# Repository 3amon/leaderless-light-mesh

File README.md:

# Leaderless light mesh

Firmware, tools, tests and hardware for small wearable LED rings that keep a
shared clock with no leader. Each ring is an nRF52840 running Zephyr and
OpenThread. Rings gossip their clocks to whoever is in radio range, agree on
who is standing together, and render the same animation on every member of
that group, pixel for pixel, with no ring in charge and nothing streamed.

People walk around. Groups split, merge and lose members all the time, so the
design treats every one of those as a non-event: there is no time master to
elect, lose or fail over.

The chart is a simulation, not a measurement: six nodes, each running the
firmware's own `clock_estimator.c`, in two groups that start 0.8 s apart and
come into range at t = 0. Data and the command that produced it are in
[`docs/data/`](docs/data/). The measured numbers are below.

## What is in here

- **A leaderless clock** in the style of GTSP (Sommer and Wattenhofer, 2009):
  every node keeps `global = h * local + theta`, pulls `theta` (phase) and `h`
  (rate) toward a trust-weighted median of its neighbours, and regresses rate
  on the neighbours' raw, never-adjusted clocks. Design in
  [`TIME-SYNC.md`](TIME-SYNC.md); wire format and policy in
  [`docs/firmware-architecture.md`](docs/firmware-architecture.md).
- **Group formation** from one-hop radio contact, with hysteresis, reciprocal
  topology and a timing gate, so "lit as a group" implies "visibly in sync".
- **Signed over-the-air updates** through MCUboot with automatic rollback, a
  transactional deployer, and a boot-recovery ladder that gets a hung node
  back to a USB drive without a button.
- **A carrier PCB** (KiCad) and **printed enclosures** (FreeCAD).
- **Fleet tools** that run on a Raspberry Pi border router.
- **Host tests and simulators** that compile the same C files the firmware
  ships.

## What was demonstrated, with numbers

Each number names the file that supports it. "Development repository" means
the private repository this was exported from; its history and its real
device inventory are not included here.

| | Number | Source |
|---|---|---|
| Sync measured optically, two rings | 301 paired LED flashes over five minutes at 30 fps: **3.59 ms** median offset, 3.11 ms MAD, -0.93 ms/min drift. A later run: 304 pairs, 4.42 ms, 3.35 ms MAD, +0.65 ms/min | `docs/development-plan.md`, "Execution log — 2026-07-21", Phase 6 |
| Same two rings before the sync engine existed | 47.8 ms apart (arbitrary phase) | `TIME-SYNC.md`, "Baseline measurement" |
| Recovery from a forced clock scramble, on camera | back in step 9.9 s after the scramble, 150 flash pairs | `evidence/hardware/2026-07-20/sync-tests/20260718-044700-scramble/result.json` |
| Fleet | 39 rings inventoried when the fleet was deployed (41 by the last commit); 24 is the designed cap for one group | development repository inventory (a 6-row sample is in `config/rings.json`); cap in `docs/firmware-architecture.md` |
| Largest group qualified on hardware | six rings re-forming one scene after a rollout; one deliberately scrambled ring was demoted in 24 s and readmitted 16 s after the abuse stopped | `docs/sync-cohesion-investigation.md`, "Live fleet qualification" |
| Largest group in simulation | 24 nodes cold-starting together converge in 29-36 s | `docs/gap-hunt-2026-08.md`, section 3 |
| Releases | 41 tagged releases, v0.1.16 to v0.1.93, over 268 commits from 2026-07-17 | development repository; process in `docs/releases.md` |
| Reproducible builds | two pristine builds byte-identical except the RSA-PSS signature salt | `docs/releases.md` |
| Fleet image size | 288,304 of 372,736 bytes flash (77.35%) at v0.1.16; the release gate is 92% | `docs/releases.md`, `scripts/check_firmware_size.py` |
| Reboot soak | 124 reboot trials archived, 121 passed, including 50/50 and 43/43 runs | `evidence/hardware/SUMMARY.md` |
| Forced rollback | final run 5/5: an image that refuses to confirm is reverted by MCUboot, in 119.86-120.63 s. Two earlier harness runs failed on their first trial and are kept | `evidence/hardware/SUMMARY.md`, `docs/development-plan.md` Phase 1 |
| USB/UF2 recovery | 36/36 trials | `evidence/hardware/SUMMARY.md` |
| OTA transactions | 28 per-device results archived: 12 `success`, 10 `already_current`, 5 `upload_failed` (uploads cut on purpose; none armed), 1 `rollback` (an image on an isolated partition that must not confirm) | `evidence/hardware/SUMMARY.md` |
| Recovery ladder | a deliberately hanging image presented itself as a USB drive 51 s after reset; the board was healthy 5.7 s after the file copy | `docs/boot-recovery-ladder.md` |
| Host tests | 212 Python tests; they build and run 22 C suites (131 test functions) against the firmware sources | `tests/`, run below |
| Simulators | 9 measurement harnesses (7 protocol, 2 rendering) plus the merge trace | `tests/c/campaign/`, `tests/c/bench/`, `tests/c/merge_trace.c` |

The archived evidence covers 2026-07-18 to 2026-07-20 and two rings. Later
results in the table are from the written record; their raw files stayed on
the gateway.

## What went wrong

- **A release was withdrawn.** v0.1.82 passed review and host tests, then
  wedged every board into its watchdog seconds after joining a live mesh: a
  struct had grown past the 4 KB main stack. v0.1.83 fixed it. The only
  "healthy" bench run of v0.1.82 had been on a quieted mesh that never
  exercised the path. `docs/gap-hunt-2026-08.md`, 2026-08-17 addendum.
- **The Rev A board has a pin-count error.** The module has 13 pins per side;
  the carrier was laid out for 12. Seated the obvious way it shorts RAW to
  ground. The battery connector is also routed to the wrong rail and must not
  be used. `docs/hardware-rev-a-errata.md`.
- **The "white flash" was a brownout.** A scene that lit every LED at once
  drew about six times the idle load for 370 ms, sagged the rail and turned
  the ring white. It looked like a colour bug and was invisible in any
  pixel-level simulation. The fix is a per-frame power budget found on the
  hardware (45 per LED); the first value tried (90) never engaged.
  `firmware/thread-ring/src/led_budget.h`, `tests/c/led_budget_test.c`.
- **A weighted mean let one liar capture the clock.** In simulation a crowd
  converged onto a node broadcasting a constant 10 s lie. The estimator now
  uses a weighted median, a snap quorum and minority-outlier rejection.
  `docs/sync-cohesion-investigation.md`.
- **A median tie-break ratcheted the fleet's rate trim** about +300 ppm per
  minute while phase stayed locked, so nothing looked wrong. Found in
  telemetry on seven live rings, reproduced in the simulator, fixed in
  v0.1.76 and kept as a regression test. Same document.
- **Still open.** An intermittent watchdog reset during the MCUboot image
  swap (`reset=00000012`) was never fixed; the node rolls back safely but the
  update does not land (`docs/onboarding-blank-boards.md`, "Failure
  signatures"). The battery-park branch of the recovery ladder was never
  qualified on hardware. Battery voltage cannot be read on Rev A.

## Limits of the evidence

- The camera measurement is of **two** rings on a bench. Larger groups were
  checked through firmware telemetry and by eye, not optically.
- Everything about 24-node behaviour is simulated.
- The simulators model the radio as per-link loss and jitter. They do not
  model 802.15.4 contention or body shadowing.
- The measurement harnesses in `tests/c/campaign/` assert nothing, and the
  engine has changed since `docs/gap-hunt-2026-08.md` was written, so their
  output today does not reproduce every figure in that report.
- The firmware in this export was **not built** as part of preparing it: the
  Thread credentials were replaced with placeholders, and a log string and a
  few comments were reworded. The host tests were run (below).

## Build, run, test

Host tests need Python 3.12 or newer and a C compiler (`cc`). No hardware, no
network.

```sh
uv run --no-project python -m unittest discover -s tests
```

212 tests; a few seconds. The simulators that print measurements:

```sh
SRC=firmware/thread-ring/src
cc -std=c11 -O2 -I$SRC -Itests/c -Itests/c/campaign \
   $SRC/group_engine.c $SRC/group_policy.c $SRC/social_scene.c \
   $SRC/peer_slot_policy.c $SRC/sync_schedule.c $SRC/clock_estimator.c \
   tests/c/campaign/integrated.c -lm -o /tmp/integrated && /tmp/integrated

cc -std=c11 -O2 -I$SRC -Itests/c $SRC/clock_estimator.c \
   tests/c/merge_trace.c -lm -o /tmp/merge_trace && /tmp/merge_trace | head
```

See `tests/c/campaign/README.md` and `tests/c/bench/README.md` for the rest.

Firmware needs Zephyr SDK 0.17.0 and the pinned workspace
(`west.yml`, `config/toolchain.lock.json`, `docs/releases.md`):

```sh
ZEPHYR_WORKSPACE=/path/to/zephyr-ws scripts/bootstrap_workspace.sh
scripts/build_firmware.sh debug
MCUBOOT_SIGNING_KEY=/secure/key.pem scripts/build_firmware.sh fleet
scripts/local_ci.sh        # the whole gate, including the native_sim test
```

Target board: a SuperMini nRF52840 (nice!nano-compatible) with the Adafruit
UF2 bootloader, Zephyr board `promicro_nrf52840/nrf52840/uf2`. Zephyr,
MCUboot, OpenThread and the UF2 bootloader are not vendored; `west` fetches
the first three.

### Network credentials

`firmware/thread-ring/prj.conf` carries **placeholder** Thread credentials:
the well-known example network key, PAN ID 0xABCD and Zephyr's default
extended PAN ID. A ring built with them will only join a network that uses
the same public values, which you should not run.

To use your own, change `CONFIG_OPENTHREAD_NETWORKKEY`, `CONFIG_OPENTHREAD_PANID`
and `CONFIG_OPENTHREAD_XPANID` (and the channel and name if you like) to match
your border router's active dataset. Keep the real values out of version
control: either edit `prj.conf` locally, or put the three lines in a private
Kconfig fragment and add it to the `EXTRA_CONF_FILE` list in
`scripts/build_firmware.sh`. The network key is the trust boundary between
rings, so treat it like a password.

### Other things you supply

- `config/rings.json` is a six-row sample with invented serial numbers and
  addresses. The fleet tools resolve every target through this file; replace
  it with your own devices.
- `config/release-signers.example` shows the allowed-signers format for
  release attestation. Copy it to `config/release-signers` with your own key.
- Firmware and release signing keys, and the per-device control keys, are
  never in the repository. `docs/security.md` describes where they live.
- The fleet tools expect a small dashboard service on the gateway
  (`http://localhost:8080`) for name lookup and heartbeat history. It belongs
  to a separate project and is not included; most tools also accept an IPv6
  address directly.

## Layout

| Path | Contents |
|---|---|
| `TIME-SYNC.md` | Protocol design notes |
| `docs/` | Architecture, release process, security model, errata, investigations. Index in `docs/README.md` |
| `firmware/thread-ring/` | The ring firmware (about 11,500 lines of C). Policy modules are pure C with no Zephyr dependencies |
| `firmware/ring-test/`, `firmware/settings-medic/` | Bring-up image and a settings-partition recovery image |
| `tests/` | Python tests; `tests/c/` C suites and simulators; `tests/zephyr/` native_sim boot/OTA test |
| `pi-tools/` | Fleet tools for the gateway: transactional deploy, control client, HIL harnesses, camera timing |
| `scripts/` | Build, release, signing, CI, workspace checks, USB helpers |
| `config/` | Sample inventory, HIL job definitions, toolchain lock |
| `patches/` | Tracked patches to MCUboot and Zephyr |
| `deploy/systemd/` | Sandboxed units for the HIL runner |
| `hardware/` | KiCad project, gerbers, BOM/CPL, renders |
| `enclosure/` | Printed enclosures and diffuser caps |
| `evidence/` | Archived hardware test results and a summary table |

## Not included, and why

- Git history and release binaries: the export is a snapshot of `main`.
- The real device inventory, control keys, signing keys and Thread
  credentials.
- Kernel logs and raw captures from the gateway (host output).
- Session handoff notes and one-off rollout scripts from the development
  repository.
- The gateway's operating-system setup and dashboard, which belong to a
  separate project.
- The two browser simulations the design was first worked out in.

## Licence

Code, tests, tools and documentation: MIT, see [`LICENSE`](LICENSE).
Hardware and enclosure design files: CC BY 4.0, see
[`LICENSE-hardware.md`](LICENSE-hardware.md). `patches/` modify Apache-2.0
projects and stay under that licence.

Copyright 2026 Eamon White <white.eamon@gmail.com>

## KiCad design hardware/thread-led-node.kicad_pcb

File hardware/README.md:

# Carrier PCB (Rev A)

KiCad 10 project for an 80 x 46 mm, 2-layer carrier that takes a SuperMini
nRF52840 module (a nice!nano-style "Pro Micro nRF52840" clone) and drives an
external WS2812B ring or strip. Design files are CC BY 4.0
(`../LICENSE-hardware.md`).

> **Rev A has two known errors. Read `../docs/hardware-rev-a-errata.md` before
> building one.**
>
> 1. The module has 13 positions per side (separate B-/B+ pins at the USB
>    end); the carrier was laid out with 12-position sockets. Seat the module
>    with B-/B+ hanging outside the sockets. Seating them in the sockets shifts
>    every pin by one and shorts RAW to ground.
> 2. J2+ is routed to RAW rather than the module's B+ charger terminal. Do not
>    connect a rechargeable battery to J2. USB and current-limited bench power
>    are verified; battery operation is not safe on Rev A.
>
> The silkscreen pin labels also print partly off the board edge.

## Files

| Path | Contents |
|---|---|
| `thread-led-node.kicad_sch`, `.kicad_pcb`, `.kicad_pro` | Schematic, board, project |
| `gerbers/` | Gerbers and Excellon drill files as sent to the fab |
| `assembly/` | BOM and placement (CPL) files for JLCPCB assembly |
| `fab_export.py` | Regenerates the fab package; computes placement centroids from pad bounding boxes and applies per-footprint rotation offsets (why: see `../docs/kicad-notes.md`) |
| `models/supermini_nrf52840.wrl` | Generated box-model stand-in for the module, used for the 3D render |
| `renders/` | 3D render, top view (PNG and SVG) |
| `thread-led-node.kicad_pcb.drc.json` | KiCad DRC report: 0 errors, 5 warnings (silkscreen), 0 unconnected |

`fab_export.py` needs KiCad's `pcbnew` Python module and `kicad-cli`. Footprints
and 3D models come from the stock KiCad libraries, which are not redistributed
here.

## Power path

- RAW -> F1 (1.1 A polyfuse) -> Q1 (AO3401A high-side switch, driven by Q2
  2N7002 with a 100 k pull-up, off at boot) -> J1 (JST-XH) to the LEDs.
- U2 (SN74LV1T34) level-shifts LED data and is powered from the fused,
  unswitched rail.
- Firmware must drive `EN_LED` (P0.17) high before the LED rail is live, wait
  for it to settle, and send black before turning it off.

## Pin map (SuperMini / nice!nano numbering)

| Signal | Pin | Board net |
|---|---|---|
| LED data out | P0.06 (J3-1) | LED_DATA_MCU -> U2 -> 330 ohm -> J1-2 |
| LED power enable | P0.17 (J3-5) | EN_LED (high = strip on) |
| USER button | P0.20 (J3-6) | BTN (to GND, internal pull-up) |
| Battery sense | P0.31 / AIN7 (J4-5) | VBAT_DIV. Measured floating on the tested modules: see the errata |

## Layout notes

- Sockets are placed so the module's USB-C face sits flush with the top board
  edge, for an enclosure wall.
- Copper pours on both layers are windowed out under the module's chip
  antenna.
- TP1 = VLED, TP2 = DIN, TP3 = GND. D3 lights when the LED rail is switched on.
- 4 x M2.5 mounting holes on a 68 x 34 mm pattern.

## BOM

| Ref | Part | LCSC |
|---|---|---|
| U2 | SN74LV1T34DBVR, SOT-23-5 | C100024 |
| Q1 | AO3401A P-FET, SOT-23 | C15127 |
| Q2 | 2N7002, SOT-23 | C8545 |
| F1 | 1206L110THYR polyfuse 1.1 A | C126818 |
| J1 | JST B3B-XH-A 3-pin | C144394 |
| J2 | JST-PH 2-pin | C126363 |
| J3, J4 | 1x12 2.54 mm female header | C7509522 |
| C1 | 100 nF 0603 | C14663 |
| C2 | 470 uF 16 V radial | C105296 |
| R1 | 330 ohm 0603 | C23138 |
| R2, R3 | 1 M 0603 | C22935 |
| R4 | 100 k 0603 | C25803 |
| R5 | 1 k 0603 | C21190 |
| D3 | red LED 0603 | C2286 |
| SW1 | 6x6 mm THT tactile | C42416242 |

Recorded cost for five assembled boards: PCB $2 + assembly $28.52, before
shipping (`../docs/kicad-notes.md`).

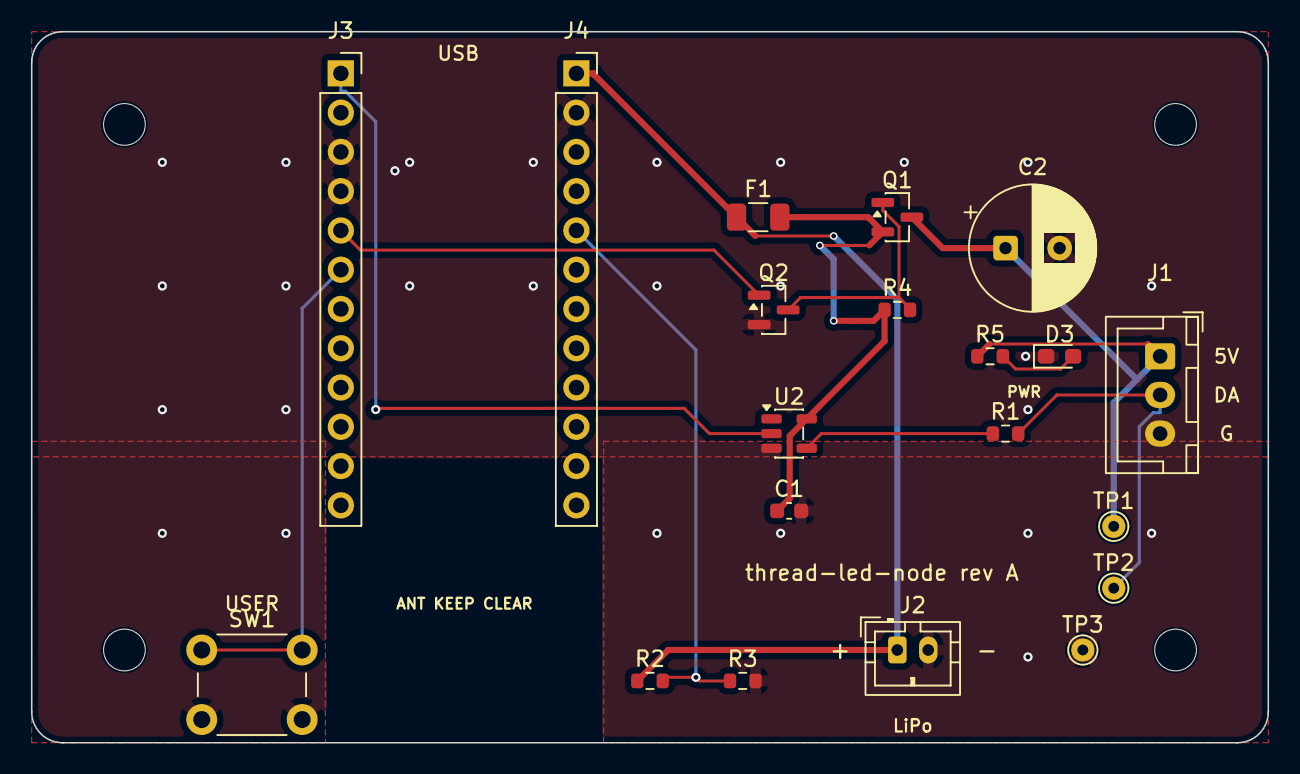
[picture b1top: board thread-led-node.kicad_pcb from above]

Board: 2 copper layers, 80.0 x 46.0 mm, 24 parts (0 on the bottom side), 12 nets.

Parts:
C1: 100nF; C_0603_1608Metric
C2: 470uF; CP_Radial_D8.0mm_P3.50mm
D3: LED_0603_1608Metric_Pad1.05x0.95mm_HandSolder
F1: 1.1A; Fuse_1206_3216Metric
J1: WS2812B_OUT; JST_XH_B3B-XH-A_1x03_P2.50mm_Vertical
J2: LiPo_1S; JST_PH_B2B-PH-K_1x02_P2.00mm_Vertical
J3: SuperMini_L; PinSocket_1x12_P2.54mm_Vertical
J4: SuperMini_R; PinSocket_1x12_P2.54mm_Vertical
MH1, MH2, MH3, MH4: MountingHole_2.7mm
Q1: AO3401A; SOT-23
Q2: 2N7002; SOT-23
R1: 330; R_0603_1608Metric
R2, R3: 1M; R_0603_1608Metric
R4: 100k; R_0603_1608Metric
R5: R_0603_1608Metric
SW1: USER; SW_PUSH_6mm
TP1, TP2, TP3: TestPoint_THTPad_D1.5mm_Drill0.7mm
U2: SN74LV1T34DBVR; SOT-23-5

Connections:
BTN: J3.6, SW1.1
EN_LED: J3.5, Q2.1
GND: C1.2, C2.2, D3.1, J1.3, J2.2, J3.3, J3.4, J4.2, Q2.2, R3.2, SW1.2, TP3.1, U2.3
LED_A: D3.2, R5.2
LED_DATA: R1.1, U2.4
LED_DATA_MCU: J3.1, U2.2
LED_DIN: J1.2, R1.2, TP2.1
Q1_GATE: Q1.1, Q2.3, R4.2
RAW: F1.1, J2.1, J4.1, R2.1
VBAT_DIV: J4.5, R2.2, R3.1
VLED: C2.1, J1.1, Q1.3, R5.1, TP1.1
VLED_F: C1.1, F1.2, Q1.2, R4.1, U2.5

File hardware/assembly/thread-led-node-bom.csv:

Comment,Designator,Footprint,LCSC Part #,JLCPCB Part #
100nF,C1,0603,C14663,C14663
470uF 16V electrolytic,C2,CP_Radial_D8.0_P3.5,C105296,C105296
LED red 0603,D3,0603,C2286,C2286
1.1A PTC resettable fuse,F1,1206,C126818,C126818
JST B3B-XH-A,J1,JST_XH_3P_vertical,C144394,C144394
JST PH 2P (W-2001S02P-K000),J2,JST_PH_2P_vertical,C126363,C126363
Female header 1x12 2.54mm,"J3,J4",PinSocket_1x12_P2.54,C7509522,C7509522
AO3401A,Q1,SOT-23,C15127,C15127
2N7002,Q2,SOT-23,C8545,C8545
330R,R1,0603,C23138,C23138
1M,"R2,R3",0603,C22935,C22935
100k,R4,0603,C25803,C25803
1k,R5,0603,C21190,C21190
Tactile 6x6 THT (SH-6X6X4.3H-CJ),SW1,SW_PUSH_6mm_THT,C42416242,C42416242
SN74LV1T34DBVR,U2,SOT-23-5,C100024,C100024
